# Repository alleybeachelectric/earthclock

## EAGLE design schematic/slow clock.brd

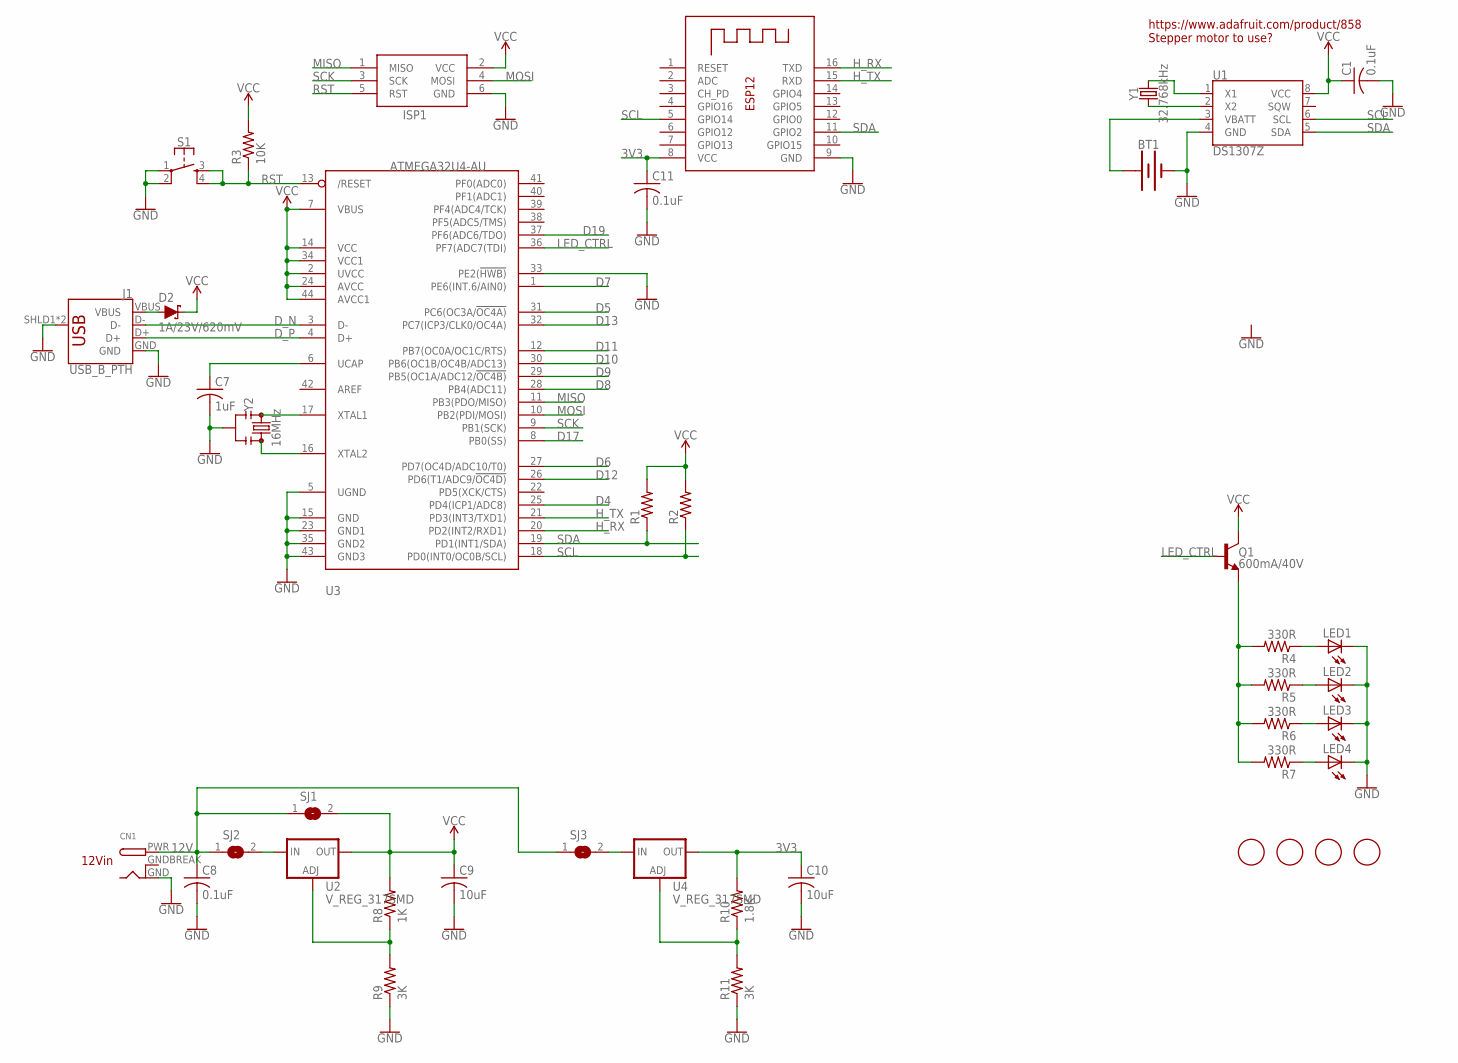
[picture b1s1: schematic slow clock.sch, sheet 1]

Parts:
BT1: BATTERY-12MM_SMD; BATTCON_12MM
C1, C8, C11: 0.1uF; C0805
C7: 1uF; C0805
C9, C10: 10uF; C0805
CN1: DCBARRELPTH; DCJACK_2MM_PTH
D2: 1A/23V/620mV; SOD-323
ISP1: AVRISP-6; AVRISP
J1: USB_B_PTH; USB-B-PTH
LED1, LED2, LED3, LED4: LEDCHIPLED_0805; CHIPLED_0805
Q1: 600mA/40V; SOT23-3
R1, R2: R-US_R0805; R0805
R3: 10K; R0805
R4, R5, R6, R7: 330R; R0805
R8: 1K; R0805
R9, R11: 3K; R0805
R10: 1.8K; R0805
S1: MOMENTARY-SWITCH-SPST-2-SMD-5.2MM; TACTILE_SWITCH_SMD_5.2MM
SJ1, SJ2, SJ3: SJ
U1: DS1307Z; SO08-0.15
U2, U4: V_REG_317SMD; SOT223
U3: ATMEGA32U4-AU; TQFP44
U$2, U$3, U$4, U$5: FIDUCIAL; FIDUCIAL_1MM
X1: ESP-12
Y1: 32.768kHz; CRYSTAL-PTH-2X6-CYL-KIT
Y2: 16MHz; RESONATOR-SMD-3.2X1.3

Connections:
3V3: C10.1, C11.1, R10.2, U4.2 (OUT), X1.8 (VCC)
12V: C8.1, CN1.PWR, SJ1.1, SJ2.1, SJ3.1; also elsewhere on the board
D4: U3.25 (PD4(ICP1/ADC8))
D5: U3.31 (PC6(OC3A/!OC4A))
D6: U3.27 (PD7(OC4D/ADC10/T0))
D7: U3.1 (PE6(INT.6/AIN0))
D8: U3.28 (PB4(ADC11))
D9: U3.29 (PB5(OC1A/ADC12/!OC4B))
D10: U3.30 (PB6(OC1B/OC4B/ADC13)); also elsewhere on the board
D11: U3.12 (PB7(OC0A/OC1C/RTS)); also elsewhere on the board
D12: U3.26 (PD6(T1/ADC9/!OC4D)); also elsewhere on the board
D13: U3.32 (PC7(ICP3/CLK0/OC4A)); also elsewhere on the board
D17: U3.8 (PB0(SS))
D19: U3.37 (PF6(ADC6/TDO))
D_N: J1.D-, U3.3 (D-)
D_P: J1.D+, U3.4 (D+)
GND: BT1.GND (-), C1.2, C7.2, C8.2, C9.2, C10.2, C11.2, CN1.GND, ISP1.6 (GND), J1.GND, J1.SHLD1 (SHIELD), J1.SHLD2 (SHIELD), LED1.C, LED2.C, LED3.C, LED4.C, R9.1, R11.1, S1.1, S1.2, U1.4 (GND), U3.5 (UGND), U3.15 (GND), U3.23 (GND1), U3.33 (PE2(!HWB)), U3.35 (GND2), U3.43 (GND3), X1.9 (GND), Y2.2; also elsewhere on the board
GNDBREAK: CN1.GNDBREAK
H_RX: U3.20 (PD2(INT2/RXD1)), X1.16 (TXD)
H_TX: U3.21 (PD3(INT3/TXD1)), X1.15 (RXD)
LED_CTRL: Q1.1 (B), U3.36 (PF7(ADC7(TDI))
MISO: ISP1.1 (MISO), U3.11 (PB3(PDO/MISO))
MOSI: ISP1.4 (MOSI), U3.10 (PB2(PDI/MOSI))
unnamed: U1.2 (X2), Y1.1
unnamed: U1.1 (X1), Y1.2
unnamed: BT1.PWR@1 (+), U1.3 (VBATT)
unnamed: U3.16 (XTAL2), Y2.3
unnamed: Q1.2 (E), R4.2, R5.2, R6.2, R7.2
unnamed: U3.17 (XTAL1), Y2.1
unnamed: D2.A, J1.VBUS
unnamed: C7.1, U3.6 (UCAP)
unnamed: LED1.A, R4.1
unnamed: LED2.A, R5.1
unnamed: LED3.A, R6.1
unnamed: LED4.A, R7.1
unnamed: SJ2.2, U2.3 (IN)
unnamed: R10.1, R11.2, U4.1 (ADJ)
unnamed: R8.1, R9.2, U2.1 (ADJ)
unnamed: SJ3.2, U4.3 (IN)
RST: ISP1.5 (RST), R3.1, S1.3, S1.4, U3.13 (/RESET)
SCK: ISP1.3 (SCK), U3.9 (PB1(SCK))
SCL: R2.1, U1.6 (SCL), U3.18 (PD0(INT0/OC0B/SCL)), X1.5 (GPIO14)
SDA: R1.1, U1.5 (SDA), U3.19 (PD1(INT1/SDA)), X1.11 (GPIO2)
VCC: C1.1, C9.1, D2.C, ISP1.2 (VCC), Q1.3 (C), R1.2, R2.2, R3.2, R8.2, SJ1.2, U1.8 (VCC), U2.2 (OUT), U3.2 (UVCC), U3.7 (VBUS), U3.14 (VCC), U3.24 (AVCC), U3.34 (VCC1), U3.44 (AVCC1); also elsewhere on the board

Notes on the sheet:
https://www.adafruit.com/product/858 Stepper motor to use?
12Vin

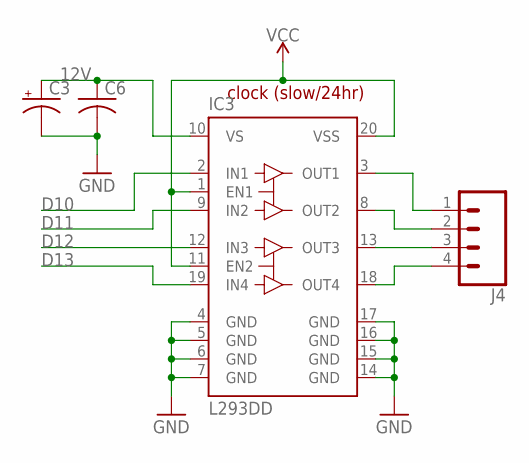
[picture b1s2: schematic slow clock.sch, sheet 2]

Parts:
C3: CPOL-USD; PANASONIC_D
C6: C-USC0805; C0805
IC3: L293DD; SO20
J4: CONN_04LOCK; 1X04_LOCK

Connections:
12V: C3.+, C6.1, IC3.10 (VS); also elsewhere on the board
D10: IC3.2 (IN1); also elsewhere on the board
D11: IC3.9 (IN2); also elsewhere on the board
D12: IC3.12 (IN3); also elsewhere on the board
D13: IC3.19 (IN4); also elsewhere on the board
GND: C3.-, C6.2, IC3.4 (GND), IC3.5 (GND), IC3.6 (GND), IC3.7 (GND), IC3.14 (GND), IC3.15 (GND), IC3.16 (GND), IC3.17 (GND); also elsewhere on the board
unnamed: IC3.3 (OUT1), J4.1
unnamed: IC3.8 (OUT2), J4.2
unnamed: IC3.13 (OUT3), J4.3
unnamed: IC3.18 (OUT4), J4.4
VCC: IC3.1 (EN1), IC3.11 (EN2), IC3.20 (VSS); also elsewhere on the board

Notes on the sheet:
clock (slow/24hr)

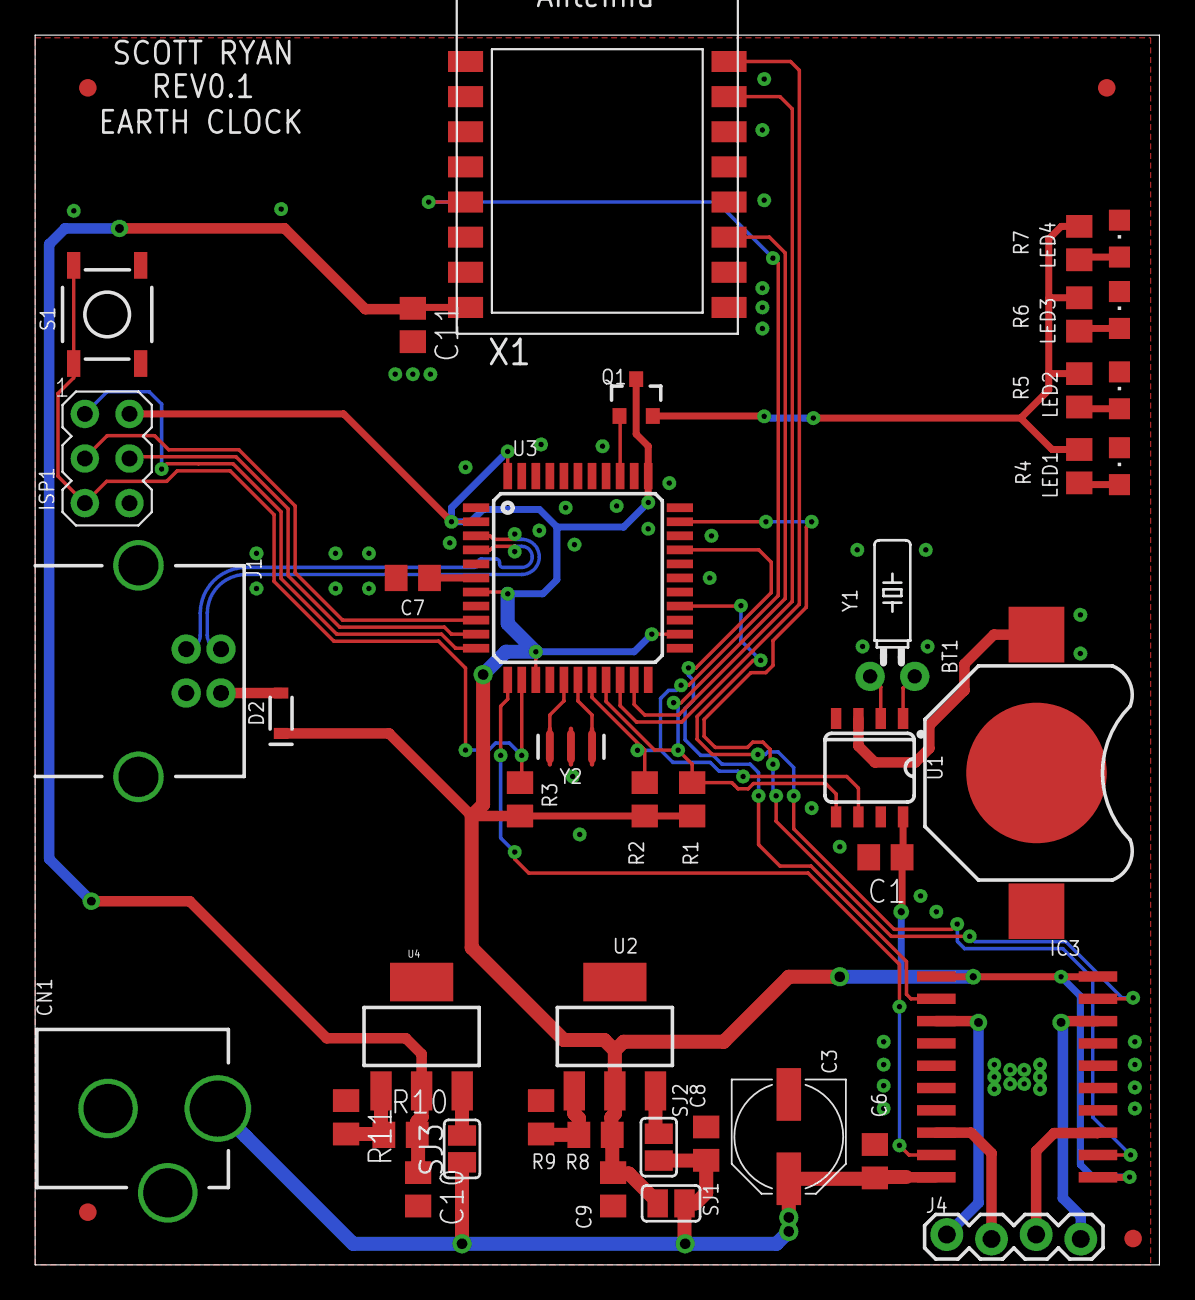
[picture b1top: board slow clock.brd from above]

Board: 2 copper layers, 64.0 x 70.0 mm, 46 parts (0 on the bottom side), 39 nets.

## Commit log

2017-10-04 initial commit
    added majority of parts. need to get polarized caps the right size, need to get passives inserted, need to get motors set up, need to get pins from atmega to driver completed.
2017-10-05 finished routing
    Added pinout for bipolar stepper motors, need to source small enough stepper for it.
    should read datasheets closer to verify H bridge can run on such little voltage (5V stepper?)
    Maybe add more decoupling caps for atmega
    maybe add through hole for LED's (so you can mount them)
2017-10-05 closer to done
    changed the motor to be driven by 12vin, inserted voltage regulator to have one power supply, constant enable. would like to condence the design a little.
2017-10-05 clean up
    clean up
2018-03-08 pushed after a while

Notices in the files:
parts and their libraries:
SparkFun-Batteries: Licensing: Creative Commons ShareAlike 4.0 International - https://creativecommons.org/licenses/by-sa/4.0
